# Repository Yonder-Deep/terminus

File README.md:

# terminus
Codebase for the Terminus Autonomous Underwater Vehicle. Developed by [Yonder Deep](http://yonderdeep.org) at UC San Diego in conjunction with [Grant Deane](https://scripps.ucsd.edu/labs/stokes/grant-deane-researcher-profile/#1483576076935-e1a1fd7e-f2ac) at the Scripps Institute of Oceanography.

## Installation

Linux/Mac
```sh
$ ./install.sh
```

For installation on windows and pinouts, wiring, and tutorials refer to [this](https://learn.adafruit.com/adafruit-bno055-absolute-orientation-sensor/arduino-code) guide on the Adafruit BNO055 sensor.

## Contributors

Ian Carrasco, Ruben Chan, Bernard Suwirjo, Raman Kathuria, Arvind Saripalli, John Duong, Christian Conaway, and Alex Smith.

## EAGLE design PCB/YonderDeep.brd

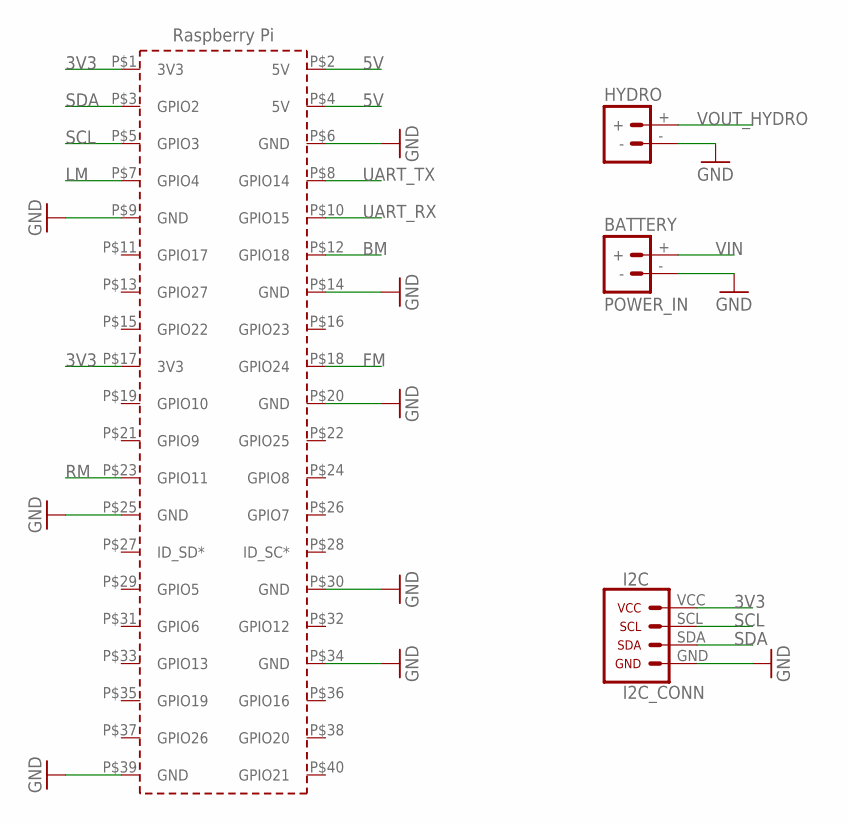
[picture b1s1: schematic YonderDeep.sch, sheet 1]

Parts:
BATTERY: POWER_IN; TERMINAL
HYDRO: POWER_IN; TERMINAL
I2C: I2C_CONN; 1X04
PCB1: RPI3; RPI3_CONN_ONLY

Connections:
3V3: I2C.VCC, PCB1.P$1 (3V3), PCB1.P$17 (3V3); also elsewhere on the board
5V: PCB1.P$2 (5V), PCB1.P$4 (5V); also elsewhere on the board
BM: PCB1.P$12 (GPIO18); also elsewhere on the board
FM: PCB1.P$18 (GPIO24); also elsewhere on the board
GND: BATTERY.-, HYDRO.-, I2C.GND, PCB1.P$6 (GND), PCB1.P$9 (GND), PCB1.P$14 (GND), PCB1.P$20 (GND), PCB1.P$25 (GND), PCB1.P$30 (GND), PCB1.P$34 (GND), PCB1.P$39 (GND); also elsewhere on the board
LM: PCB1.P$7 (GPIO4); also elsewhere on the board
RM: PCB1.P$23 (GPIO11); also elsewhere on the board
SCL: I2C.SCL, PCB1.P$5 (GPIO3); also elsewhere on the board
SDA: I2C.SDA, PCB1.P$3 (GPIO2); also elsewhere on the board
UART_RX: PCB1.P$10 (GPIO15); also elsewhere on the board
UART_TX: PCB1.P$8 (GPIO14); also elsewhere on the board
VIN: BATTERY.+; also elsewhere on the board
VOUT_HYDRO: HYDRO.+; also elsewhere on the board

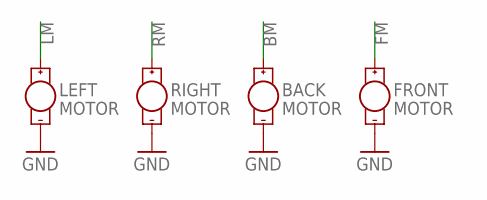
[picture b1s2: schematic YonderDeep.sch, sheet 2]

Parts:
BACK: MOTOR; 1X02_PLUS_MINUS
FRONT: MOTOR; 1X02_PLUS_MINUS
LEFT: MOTOR; 1X02_PLUS_MINUS
RIGHT: MOTOR; 1X02_PLUS_MINUS

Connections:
BM: BACK.+; also elsewhere on the board
FM: FRONT.+; also elsewhere on the board
GND: BACK.-, FRONT.-, LEFT.-, RIGHT.-; also elsewhere on the board
LM: LEFT.+; also elsewhere on the board
RM: RIGHT.+; also elsewhere on the board

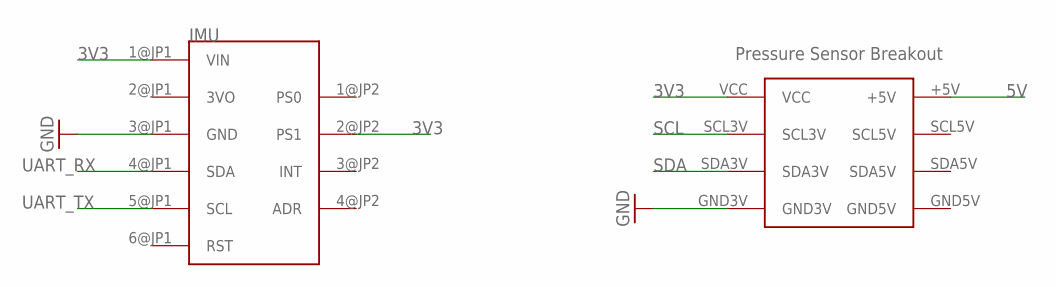
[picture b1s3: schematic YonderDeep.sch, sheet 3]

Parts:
IMU: BNO055
U$1: PRESSURE_SENSOR_BREAKOUT; BLUEROBOTICS_I2C_LVL_SHFT

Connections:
3V3: IMU.1@JP1 (VIN), IMU.2@JP2 (PS1), U$1.VCC; also elsewhere on the board
5V: U$1.+5V; also elsewhere on the board
GND: IMU.3@JP1 (GND), U$1.GND3V; also elsewhere on the board
SCL: U$1.SCL3V; also elsewhere on the board
SDA: U$1.SDA3V; also elsewhere on the board
UART_RX: IMU.4@JP1 (SDA); also elsewhere on the board
UART_TX: IMU.5@JP1 (SCL); also elsewhere on the board

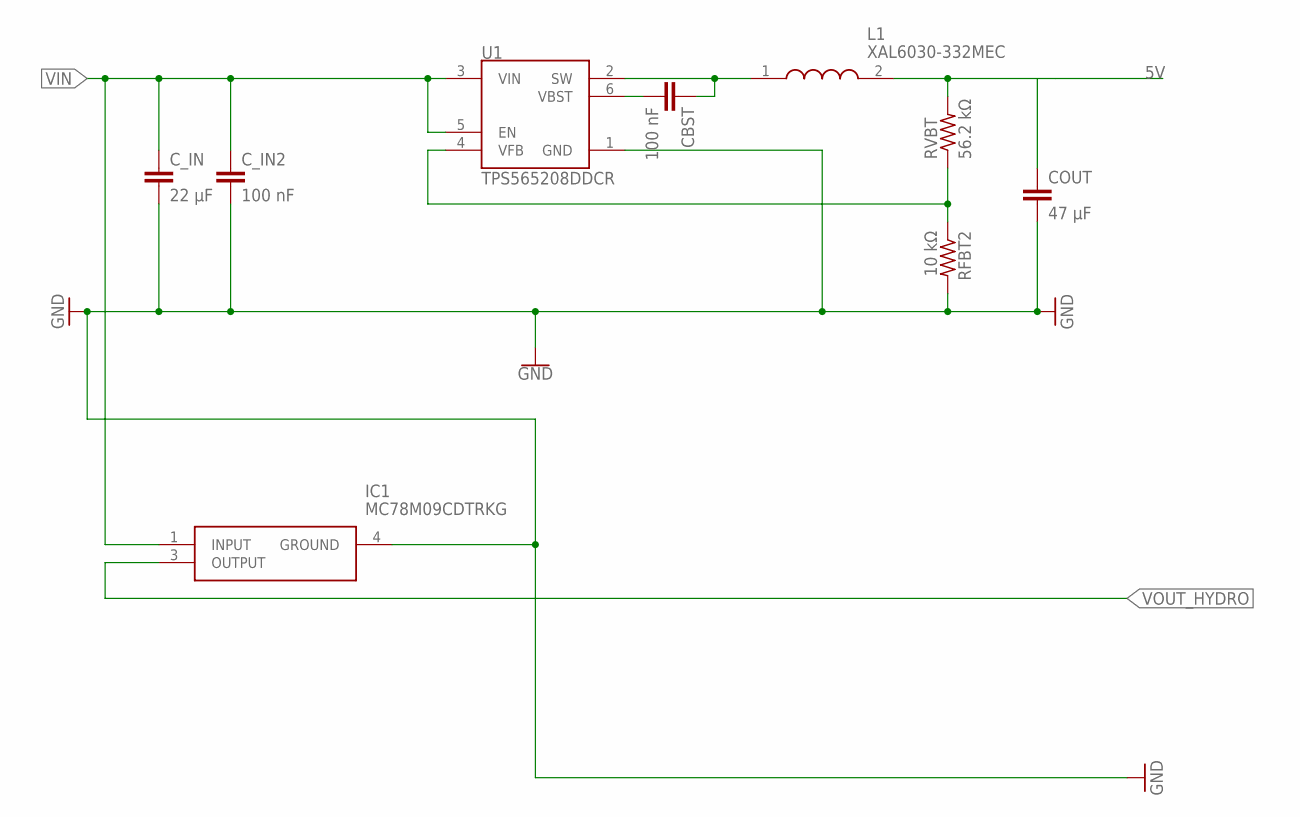
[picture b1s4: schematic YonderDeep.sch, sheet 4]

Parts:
CBST: 100 nF; C0603K
COUT: 47 µF; C1210K
C_IN: 22 µF; C1206K
C_IN2: 100 nF; C0603K
IC1: MC78M09CDTRKG; TO229P991X238-4_3N
L1: XAL6030-332MEC; XAL6030-122MEB
RFBT2: 10 kΩ; RESC1005X40
RVBT: 56.2 kΩ; R0402
U1: TPS565208DDCR; SOT95P280X110-6N

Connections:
5V: COUT.1, L1.2, RVBT.2; also elsewhere on the board
GND: COUT.2, C_IN.2, C_IN2.2, IC1.4 (GROUND), RFBT2.2, U1.1 (GND); also elsewhere on the board
unnamed: CBST.2, U1.6 (VBST)
unnamed: CBST.1, L1.1, U1.2 (SW)
unnamed: RFBT2.1, RVBT.1, U1.4 (VFB)
VIN: C_IN.1, C_IN2.1, IC1.1 (INPUT), U1.3 (VIN), U1.5 (EN); also elsewhere on the board
VOUT_HYDRO: IC1.3 (OUTPUT); also elsewhere on the board

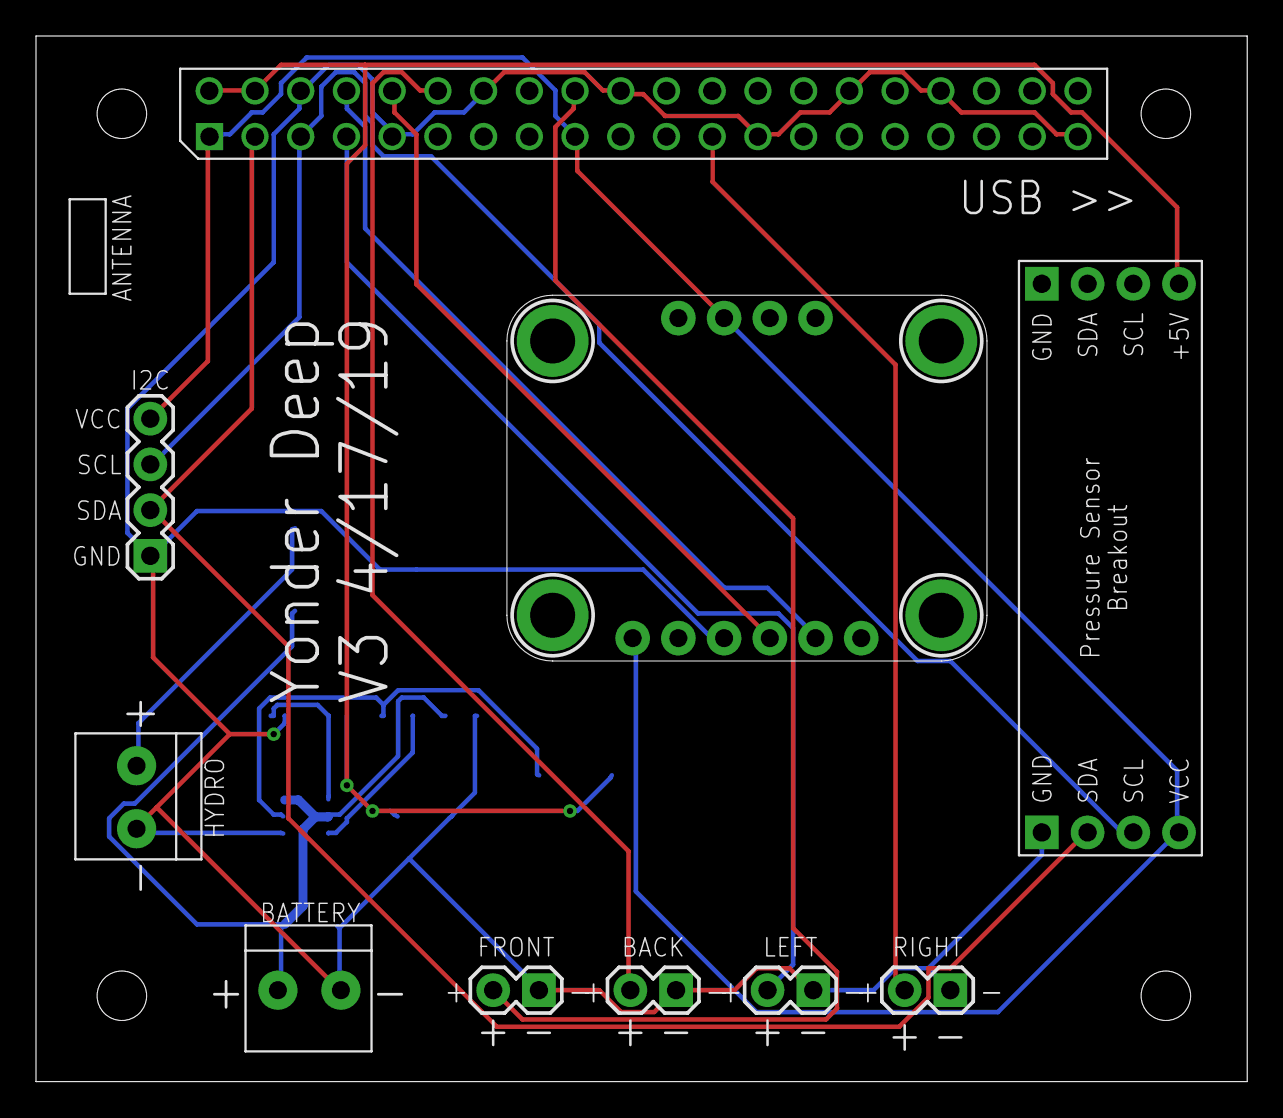
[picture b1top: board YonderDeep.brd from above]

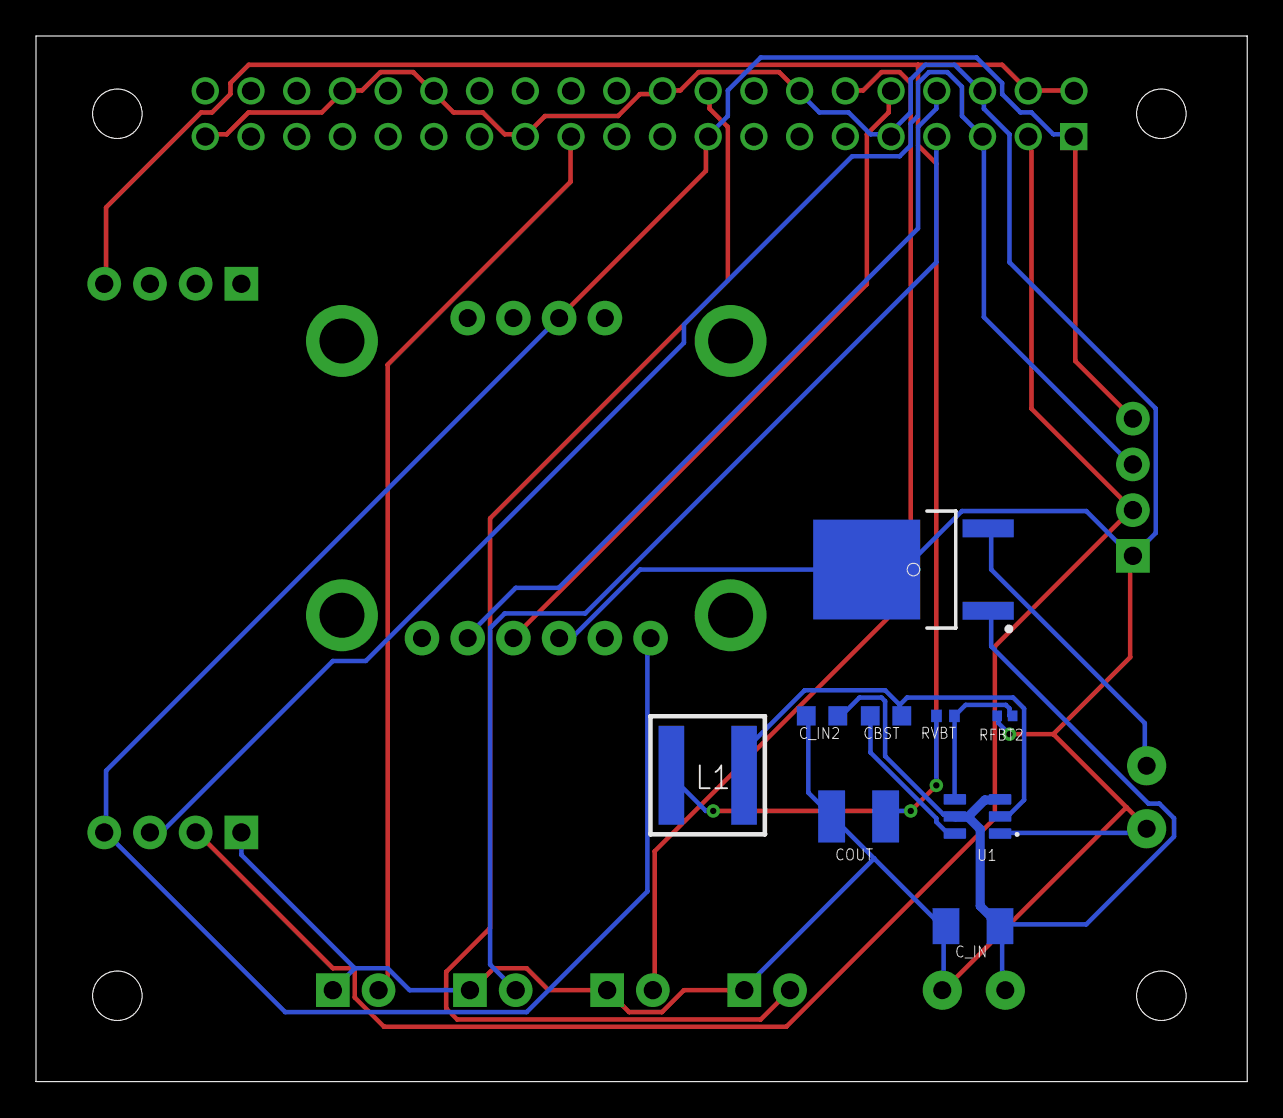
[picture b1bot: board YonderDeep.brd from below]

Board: 2 copper layers, 67.3 x 58.1 mm, 19 parts (9 on the bottom side), 16 nets.

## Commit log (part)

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2018-02-23 Added installation script for UNIX.
2018-02-23 Added testbed code. Need hydrophone and ROS code.
2018-02-27 Added hydrophone testing program
2018-03-31 Added auv startup scripts
2018-03-31 Modified startup script for auv. Works on boot.
2018-03-31 Checking packet loss.
2018-04-01 Adding auv radio test script
2018-04-01 Fixed variable name MOTOR -> MOTOR_INDEX
2018-04-13 Added communication calibration
2018-04-14 Created Archive folder for all Archived files
2018-04-14 Refactoring base station code
2018-05-05 added gitignore file
2018-05-06 Added React UI
2018-05-06 basic ui
2018-05-19 Added center (back) motor
2018-10-27 base station radio test script (confusing classes/structure - need to rework)
2018-10-27 Moved Motor to its own class
2018-10-27 Updated baseStation and NavController
2018-10-27 Removed DS_Store and added to gitignore.
2018-11-03 Refactored Motor Code
2018-11-03 Changed import in AUV and base station so that components folder can be imported.
2018-11-10 Added debug flag to navigation module.
2018-11-10 Refactor base_station.py
2018-11-10 Added radio test file for AUV.
2018-11-17 Updated README with installation and run instructions.
2018-11-17 Minor change to README
2018-11-17 Pulled in from develop and resolved errors.
2018-11-17 Modified Radio Test
2018-11-18 Added file logging capability
2018-11-27 Modified AUV to run on startup and to restart auv run loop when disconnected from base station.
2018-12-04 Edited Basestation for system test one
2019-01-12 incorrect indentations
2019-02-13 updated startup.sh
2019-02-13 modified auv and startup.sh
2019-02-13 modified example for pressure sensor
2019-02-13 updated motor_controller
2019-02-13 base_station now includes ballasting
2019-02-13 this is a test commit
2019-02-13 updated nav.py to include ballasting
2019-02-13 PCB V1
2019-02-20 pid v1
2019-02-20 integrated pid into auv
2019-02-27 updated pid
2019-03-02 outline of gui
2019-03-02 mission x, y map
2019-03-05 mission_map module
2019-03-06 Updated Mission Map Object
2019-03-07 Added a force-quit function for GUI
2019-03-09 added calibrate motor sections, can addwaypoint using button, switched adding waypoint to using left click, added console for logging
2019-03-09 added baudrate parameter when creating serial object (defaults to 115200)
2019-03-12 logger, resized windows, swapped console and calibration positions
2019-03-13 Tweaked debug and Code style
2019-03-13 working pid
2019-04-06 axis conversion from latlon to utm
2019-04-13 New Data-Packet in AUV.py, changes to nav.py and motor_controller.py
2019-04-13 Updated AUV.py with more functions!
2019-04-13 heading calc and test
2019-04-13 Updated AUV.py
2019-04-18 gps test
2019-04-18 removed waypoint mainloop from map, base_station incorporates calibrating individudal motor
2019-04-25 state machine init
2019-04-25 Updated main.py and base_station.py
2019-04-25 Refactored base_station.py
2019-04-25 Added auv param to state ctor
2019-04-25 update logging for state machine
2019-04-25 fix import path
2019-04-28 init sensor state fix
2019-05-02 abstract out radio code
2019-05-02 refactor main, add in_waiting
2019-05-04 gps tests
2019-05-04 ctrl c work when runnign with gps
2019-05-09 json io bug fix and tests
2019-05-11 updated base_station and nav.py
2019-05-11 fixed some bugs in base_station.py
2019-05-11 update in_waiting
2019-05-11 debug states
2019-05-11 fix#1
2019-05-11 fix#3
2019-05-11 debug#5
2019-05-11 fix#6
2019-05-11 fix#7
2019-05-11 add CAL state, refactor
2019-05-11 Fix#8
2019-05-11 fix#10
2019-05-11 fix#12
2019-05-16 new persistent state implementation
2019-05-16 debug#14
2019-05-16 refactor
2019-05-16 fix#16
2019-05-16 update manual control timeout
2019-05-16 debug#19
2019-05-16 fix#20
2019-05-16 cleanup#21
2019-05-16 cleanup#23
2019-05-16 debug#24
2019-05-18 bal in progress
2019-05-18 add timeout check and status state
2019-05-18 debug#25
2019-05-18 fix#27
2019-05-18 fix#29
2019-05-18 debug#30
2019-05-18 debug#32
2019-05-18 fix#33
2019-05-18 fix#34
2019-05-18 fix#36
2019-05-23 add gps testing
2019-05-23 add gps state
2019-05-25 fix pressure sensor not reading
2019-05-30 test w/o gps
2019-06-01 Added battery components folder
2019-12-29 Bump handlebars from 4.0.11 to 4.5.3 in /GUI/ui
    Bumps [handlebars](https://github.com/wycats/handlebars.js) from 4.0.11 to 4.5.3.
    - [Release notes](https://github.com/wycats/handlebars.js/releases)
    - [Changelog](https://github.com/wycats/handlebars.js/blob/master/release-notes.md)
    - [Commits](https://github.com/wycats/handlebars.js/compare/v4.0.11...v4.5.3)
2020-07-30 Bump elliptic from 6.4.0 to 6.5.3 in /GUI/ui
    Bumps [elliptic](https://github.com/indutny/elliptic) from 6.4.0 to 6.5.3.
    - [Release notes](https://github.com/indutny/elliptic/releases)
    - [Commits](https://github.com/indutny/elliptic/compare/v6.4.0...v6.5.3)
2020-09-05 Bump handlebars from 4.0.11 to 4.7.6 in /GUI/ui
    Bumps [handlebars](https://github.com/wycats/handlebars.js) from 4.0.11 to 4.7.6.
    - [Release notes](https://github.com/wycats/handlebars.js/releases)
    - [Changelog](https://github.com/handlebars-lang/handlebars.js/blob/master/release-notes.md)
    - [Commits](https://github.com/wycats/handlebars.js/compare/v4.0.11...v4.7.6)
2020-12-11 Bump ini from 1.3.5 to 1.3.7 in /GUI/ui
    Bumps [ini](https://github.com/isaacs/ini) from 1.3.5 to 1.3.7.
    - [Release notes](https://github.com/isaacs/ini/releases)
    - [Commits](https://github.com/isaacs/ini/compare/v1.3.5...v1.3.7)
2021-01-05 Bump axios from 0.18.0 to 0.21.1 in /GUI/ui
    Bumps [axios](https://github.com/axios/axios) from 0.18.0 to 0.21.1.
    - [Release notes](https://github.com/axios/axios/releases)
    - [Changelog](https://github.com/axios/axios/blob/v0.21.1/CHANGELOG.md)
    - [Commits](https://github.com/axios/axios/compare/v0.18.0...v0.21.1)
2021-03-01 Bump urijs from 1.19.1 to 1.19.6 in /GUI/ui
    Bumps [urijs](https://github.com/medialize/URI.js) from 1.19.1 to 1.19.6.
    - [Release notes](https://github.com/medialize/URI.js/releases)
    - [Changelog](https://github.com/medialize/URI.js/blob/gh-pages/CHANGELOG.md)
    - [Commits](https://github.com/medialize/URI.js/compare/v1.19.1...v1.19.6)
2021-03-12 Bump react-dev-utils from 5.0.1 to 5.0.3 in /GUI/ui
    Bumps [react-dev-utils](https://github.com/facebook/create-react-app/tree/HEAD/packages/react-dev-utils) from 5.0.1 to 5.0.3.
    - [Release notes](https://github.com/facebook/create-react-app/releases)
    - [Changelog](https://github.com/facebook/create-react-app/blob/master/CHANGELOG-1.x.md)
    - [Commits](https://github.com/facebook/create-react-app/commits/react-error-overlay@5.0.3/packages/react-dev-utils)
2021-03-12 Bump extend from 3.0.1 to 3.0.2 in /GUI/ui
    Bumps [extend](https://github.com/justmoon/node-extend) from 3.0.1 to 3.0.2.
    - [Release notes](https://github.com/justmoon/node-extend/releases)
    - [Changelog](https://github.com/justmoon/node-extend/blob/main/CHANGELOG.md)
    - [Commits](https://github.com/justmoon/node-extend/compare/v3.0.1...v3.0.2)
2021-03-12 Bump stringstream from 0.0.5 to 0.0.6 in /GUI/ui
    Bumps [stringstream](https://github.com/mhart/StringStream) from 0.0.5 to 0.0.6.
    - [Release notes](https://github.com/mhart/StringStream/releases)
    - [Commits](https://github.com/mhart/StringStream/compare/v0.0.5...v0.0.6)
2021-03-12 Bump mixin-deep from 1.3.1 to 1.3.2 in /GUI/ui
    Bumps [mixin-deep](https://github.com/jonschlinkert/mixin-deep) from 1.3.1 to 1.3.2.
    - [Release notes](https://github.com/jonschlinkert/mixin-deep/releases)
    - [Commits](https://github.com/jonschlinkert/mixin-deep/compare/1.3.1...1.3.2)
2021-05-07 Bump ua-parser-js from 0.7.18 to 0.7.28 in /GUI/ui
    Bumps [ua-parser-js](https://github.com/faisalman/ua-parser-js) from 0.7.18 to 0.7.28.
    - [Release notes](https://github.com/faisalman/ua-parser-js/releases)
    - [Commits](https://github.com/faisalman/ua-parser-js/compare/0.7.18...0.7.28)
2021-05-07 Bump handlebars from 4.0.11 to 4.7.7 in /GUI/ui
    Bumps [handlebars](https://github.com/wycats/handlebars.js) from 4.0.11 to 4.7.7.
    - [Release notes](https://github.com/wycats/handlebars.js/releases)
    - [Changelog](https://github.com/handlebars-lang/handlebars.js/blob/master/release-notes.md)
    - [Commits](https://github.com/wycats/handlebars.js/compare/v4.0.11...v4.7.7)
2021-05-12 Bump merge from 1.2.0 to 1.2.1 in /GUI/ui
    Bumps [merge](https://github.com/yeikos/js.merge) from 1.2.0 to 1.2.1.
    - [Release notes](https://github.com/yeikos/js.merge/releases)
    - [Commits](https://github.com/yeikos/js.merge/compare/v1.2.0...v1.2.1)
2021-07-20 Bump urijs from 1.19.1 to 1.19.7 in /GUI/ui
    Bumps [urijs](https://github.com/medialize/URI.js) from 1.19.1 to 1.19.7.
    - [Release notes](https://github.com/medialize/URI.js/releases)
    - [Changelog](https://github.com/medialize/URI.js/blob/gh-pages/CHANGELOG.md)
    - [Commits](https://github.com/medialize/URI.js/compare/v1.19.1...v1.19.7)
    ---
    updated-dependencies:
2021-08-04 Bump tar from 4.4.2 to 4.4.15 in /GUI/ui
    Bumps [tar](https://github.com/npm/node-tar) from 4.4.2 to 4.4.15.
    - [Release notes](https://github.com/npm/node-tar/releases)
    - [Changelog](https://github.com/npm/node-tar/blob/main/CHANGELOG.md)
    - [Commits](https://github.com/npm/node-tar/compare/v4.4.2...v4.4.15)
    ---
    updated-dependencies:
2021-09-01 Bump tar from 4.4.2 to 4.4.19 in /GUI/ui
    Bumps [tar](https://github.com/npm/node-tar) from 4.4.2 to 4.4.19.
    - [Release notes](https://github.com/npm/node-tar/releases)
    - [Changelog](https://github.com/npm/node-tar/blob/main/CHANGELOG.md)
    - [Commits](https://github.com/npm/node-tar/compare/v4.4.2...v4.4.19)
    ---
    updated-dependencies:
2022-01-13 Bump follow-redirects from 1.4.1 to 1.14.7 in /GUI/ui
    Bumps [follow-redirects](https://github.com/follow-redirects/follow-redirects) from 1.4.1 to 1.14.7.
    - [Release notes](https://github.com/follow-redirects/follow-redirects/releases)
    - [Commits](https://github.com/follow-redirects/follow-redirects/compare/v1.4.1...v1.14.7)
    ---
    updated-dependencies:
    - dependency-name: follow-redirects
2022-02-11 Bump chownr from 1.0.1 to 1.1.4 in /GUI/ui
    Bumps [chownr](https://github.com/isaacs/chownr) from 1.0.1 to 1.1.4.
    - [Release notes](https://github.com/isaacs/chownr/releases)
    - [Commits](https://github.com/isaacs/chownr/compare/v1.0.1...v1.1.4)
    ---
    updated-dependencies:
    - dependency-name: chownr
2022-02-26 Bump urijs from 1.19.1 to 1.19.8 in /GUI/ui
    Bumps [urijs](https://github.com/medialize/URI.js) from 1.19.1 to 1.19.8.
    - [Release notes](https://github.com/medialize/URI.js/releases)
    - [Changelog](https://github.com/medialize/URI.js/blob/gh-pages/CHANGELOG.md)
    - [Commits](https://github.com/medialize/URI.js/compare/v1.19.1...v1.19.8)
    ---
    updated-dependencies:
2022-03-08 Bump urijs from 1.19.1 to 1.19.10 in /GUI/ui
    Bumps [urijs](https://github.com/medialize/URI.js) from 1.19.1 to 1.19.10.
    - [Release notes](https://github.com/medialize/URI.js/releases)
    - [Changelog](https://github.com/medialize/URI.js/blob/gh-pages/CHANGELOG.md)
    - [Commits](https://github.com/medialize/URI.js/compare/v1.19.1...v1.19.10)
    ---
    updated-dependencies:
2022-04-12 Bump urijs from 1.19.1 to 1.19.11 in /GUI/ui
    Bumps [urijs](https://github.com/medialize/URI.js) from 1.19.1 to 1.19.11.
    - [Release notes](https://github.com/medialize/URI.js/releases)
    - [Changelog](https://github.com/medialize/URI.js/blob/gh-pages/CHANGELOG.md)
    - [Commits](https://github.com/medialize/URI.js/compare/v1.19.1...v1.19.11)
    ---
    updated-dependencies:

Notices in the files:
parts and their libraries:
SparkFun-PowerSymbols: Licensing: Creative Commons ShareAlike 4.0 International - https://creativecommons.org/licenses/by-sa/4.0
